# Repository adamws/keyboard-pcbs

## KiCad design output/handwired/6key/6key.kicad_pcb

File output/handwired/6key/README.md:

## handwired/6key

[layout](6key-kle.json) - [PCB](6key.kicad_pcb)

{:loading="lazy"}

[Open in keyboard-layout-editor](http://www.keyboard-layout-editor.com/##@@=0,0&=0,1&=0,2;&@=1,0&=1,1&=1,2)

{:loading="lazy"}

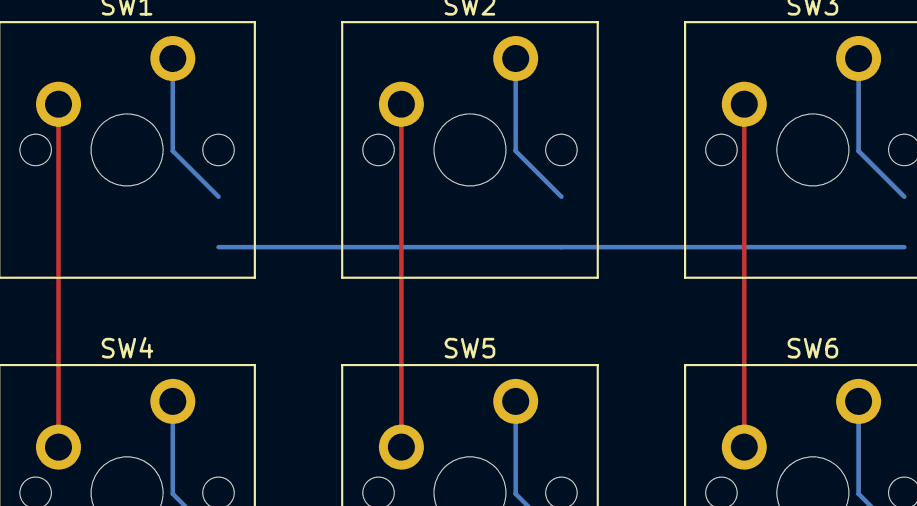
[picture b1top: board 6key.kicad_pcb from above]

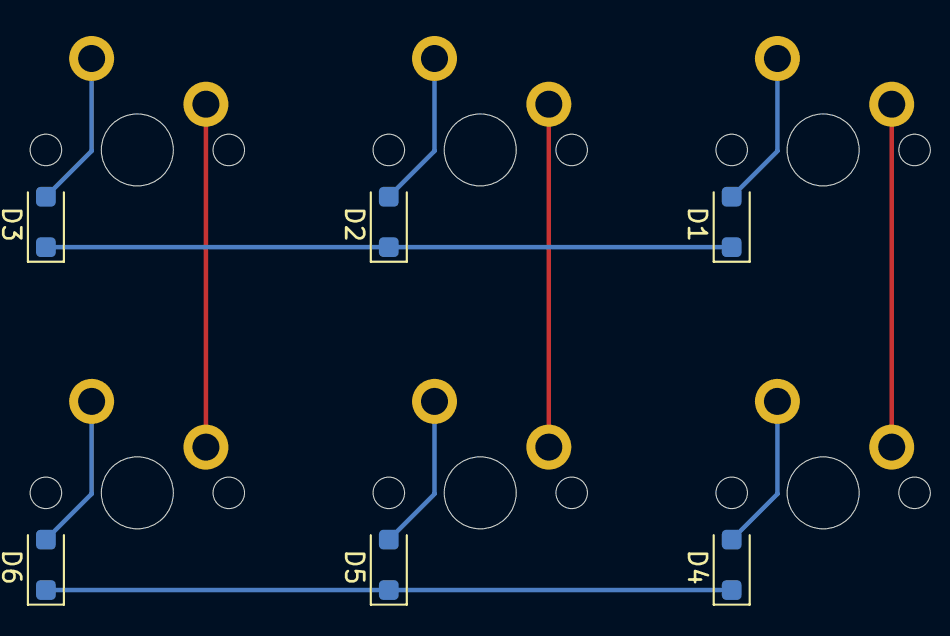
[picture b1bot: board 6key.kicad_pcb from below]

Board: 2 copper layers, 12 parts (6 on the bottom side), 11 nets.

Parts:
D1, D2, D3, D4, D5, D6: D_SOD-123F
SW1, SW2, SW3, SW4, SW5, SW6: SW_Cherry_MX_PCB_1.00u

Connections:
COL0: SW1.1, SW4.1
COL1: SW2.1, SW5.1
COL2: SW3.1, SW6.1
unnamed: D1.2, SW1.2
unnamed: D2.2, SW2.2
unnamed: D3.2, SW3.2
unnamed: D4.2, SW4.2
unnamed: D5.2, SW5.2
unnamed: D6.2, SW6.2
ROW0: D1.1, D2.1, D3.1
ROW1: D4.1, D5.1, D6.1

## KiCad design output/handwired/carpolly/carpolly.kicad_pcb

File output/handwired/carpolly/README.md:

## handwired/carpolly

[layout](carpolly-kle.json) - [PCB](carpolly.kicad_pcb)

{:loading="lazy"}

[Open in keyboard-layout-editor](http://www.keyboard-layout-editor.com/##@@=0,0&=0,1&=0,2&=0,3&=0,4&=0,5&=0,6&=0,7&=0,8&=0,9&=0,10&_w:1.75;&=0,11;&@_w:1.25;&=1,0&=1,1&=1,2&=1,3&=1,4&=1,5&=1,6&=1,7&=1,8&=1,9&=1,10&_w:1.5;&=1,11;&@_w:1.75;&=2,0&=2,2&=2,3&=2,4&=2,5&=2,6&=2,7&=2,8&=2,9&=2,10&=2,11&=2,12;&@_w:1.25;&=3,0&=3,1&_w:1.25;&=3,2&_w:6.25;&=3,6&=3,10&=3,11&=3,12)

{:loading="lazy"}

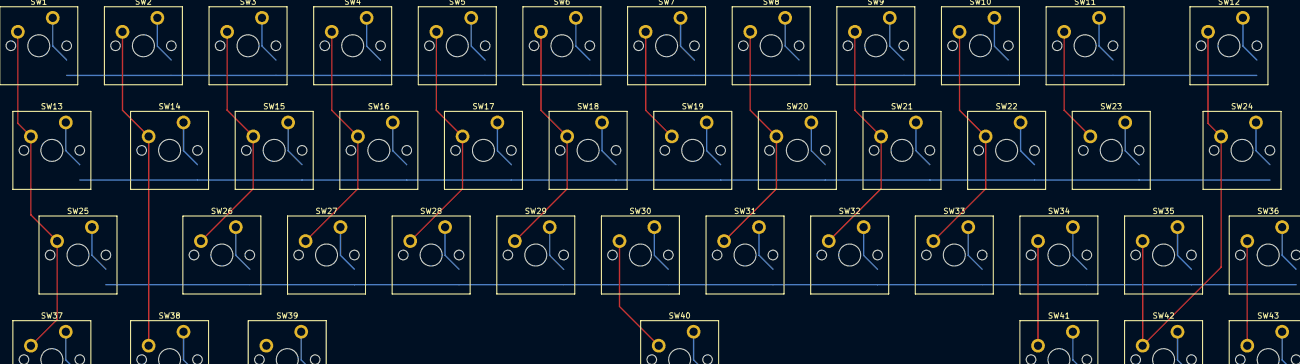
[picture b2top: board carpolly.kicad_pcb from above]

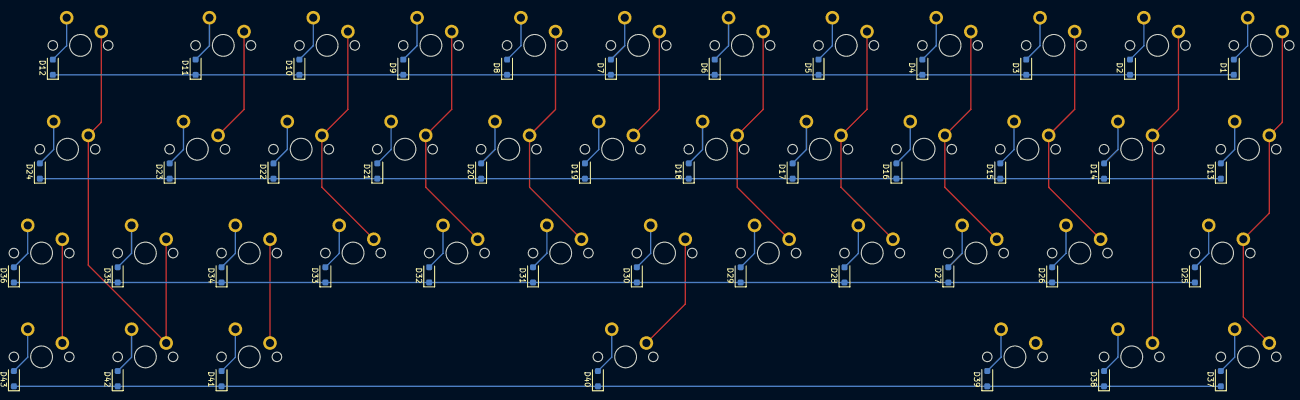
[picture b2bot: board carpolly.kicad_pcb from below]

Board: 2 copper layers, 86 parts (43 on the bottom side), 60 nets.

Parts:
D1, D2, D3, D4, D5, D6, D7, D8, D9, D10, D11, D12, D13, D14, D15, D16, D17, D18, D19, D20, D21, D22, D23, D24, D25, D26, D27, D28, D29, D30, D31, D32, D33, D34, D35, D36, D37, D38, D39, D40, D41, D42, D43: D_SOD-123F
SW1, SW2, SW3, SW4, SW5, SW6, SW7, SW8, SW9, SW10, SW11, SW12, SW13, SW14, SW15, SW16, SW17, SW18, SW19, SW20, SW21, SW22, SW23, SW24, SW25, SW26, SW27, SW28, SW29, SW30, SW31, SW32, SW33, SW34, SW35, SW36, SW37, SW38, SW39, SW40, SW41, SW42, SW43: SW_Cherry_MX_PCB_1.00u

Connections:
COL0: SW1.1, SW13.1, SW25.1, SW37.1
COL1: SW2.1, SW14.1, SW38.1
COL2: SW3.1, SW15.1, SW26.1, SW39.1
COL3: SW4.1, SW16.1, SW27.1
COL4: SW5.1, SW17.1, SW28.1
COL5: SW6.1, SW18.1, SW29.1
COL6: SW7.1, SW19.1, SW30.1, SW40.1
COL7: SW8.1, SW20.1, SW31.1
COL8: SW9.1, SW21.1, SW32.1
COL9: SW10.1, SW22.1, SW33.1
COL10: SW11.1, SW23.1, SW34.1, SW41.1
COL11: SW12.1, SW24.1, SW35.1, SW42.1
COL12: SW36.1, SW43.1
unnamed: D1.2, SW1.2
unnamed: D2.2, SW2.2
unnamed: D3.2, SW3.2
unnamed: D4.2, SW4.2
unnamed: D5.2, SW5.2
unnamed: D6.2, SW6.2
unnamed: D7.2, SW7.2
unnamed: D8.2, SW8.2
unnamed: D9.2, SW9.2
unnamed: D10.2, SW10.2
unnamed: D11.2, SW11.2
unnamed: D12.2, SW12.2
unnamed: D13.2, SW13.2
unnamed: D14.2, SW14.2
unnamed: D15.2, SW15.2
unnamed: D16.2, SW16.2
unnamed: D17.2, SW17.2
unnamed: D18.2, SW18.2
unnamed: D19.2, SW19.2
unnamed: D20.2, SW20.2
unnamed: D21.2, SW21.2
unnamed: D22.2, SW22.2
unnamed: D23.2, SW23.2
unnamed: D24.2, SW24.2
unnamed: D25.2, SW25.2
unnamed: D26.2, SW26.2
unnamed: D27.2, SW27.2
unnamed: D28.2, SW28.2
unnamed: D29.2, SW29.2
unnamed: D30.2, SW30.2
unnamed: D31.2, SW31.2
unnamed: D32.2, SW32.2
unnamed: D33.2, SW33.2
unnamed: D34.2, SW34.2
unnamed: D35.2, SW35.2
unnamed: D36.2, SW36.2
unnamed: D37.2, SW37.2
unnamed: D38.2, SW38.2
unnamed: D39.2, SW39.2
unnamed: D40.2, SW40.2
unnamed: D41.2, SW41.2
unnamed: D42.2, SW42.2
unnamed: D43.2, SW43.2
ROW0: D1.1, D2.1, D3.1, D4.1, D5.1, D6.1, D7.1, D8.1, D9.1, D10.1, D11.1, D12.1
ROW1: D13.1, D14.1, D15.1, D16.1, D17.1, D18.1, D19.1, D20.1, D21.1, D22.1, D23.1, D24.1
ROW2: D25.1, D26.1, D27.1, D28.1, D29.1, D30.1, D31.1, D32.1, D33.1, D34.1, D35.1, D36.1
ROW3: D37.1, D38.1, D39.1, D40.1, D41.1, D42.1, D43.1
